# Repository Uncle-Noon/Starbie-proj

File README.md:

<h1>STARBOY</h1>  <br>
 
// my pcb <br> 

<br>
// original starbie image 

Starbie is a tiny motion-controlled digital pet: basically a desktop Tamagotchi with minimal gameplay buttons. Instead of pressing controls, you interact with it by physically moving the board. <br>

<h1><u>WHAT IT IS </u> <br></h1>

Starbie is designed to sit on your desk, show its personality on a small display, and react to how you handle it. Tilting, moving, and otherwise checking in on your pet are meant to be part of the experience.

The board includes a microcontroller, display, motion sensor, and environmental sensor in a compact PCB design. It is USB powered and built around beginner-friendly through-hole soldering for the add-on components. <br> 

<h3> Tutorial Link -> </h3>  https://github.com/SharKingStudios/Starbie/blob/main/README.md <br> <br> 
This is my github repo for HalfLife-HackClub program. Look into the tutorial link for more information. <br >
This repo contains my devlogs, required files, and the BOM with the Starbie.ino. <br>

{P.S. I named my project Starboy instead of Starbiee}

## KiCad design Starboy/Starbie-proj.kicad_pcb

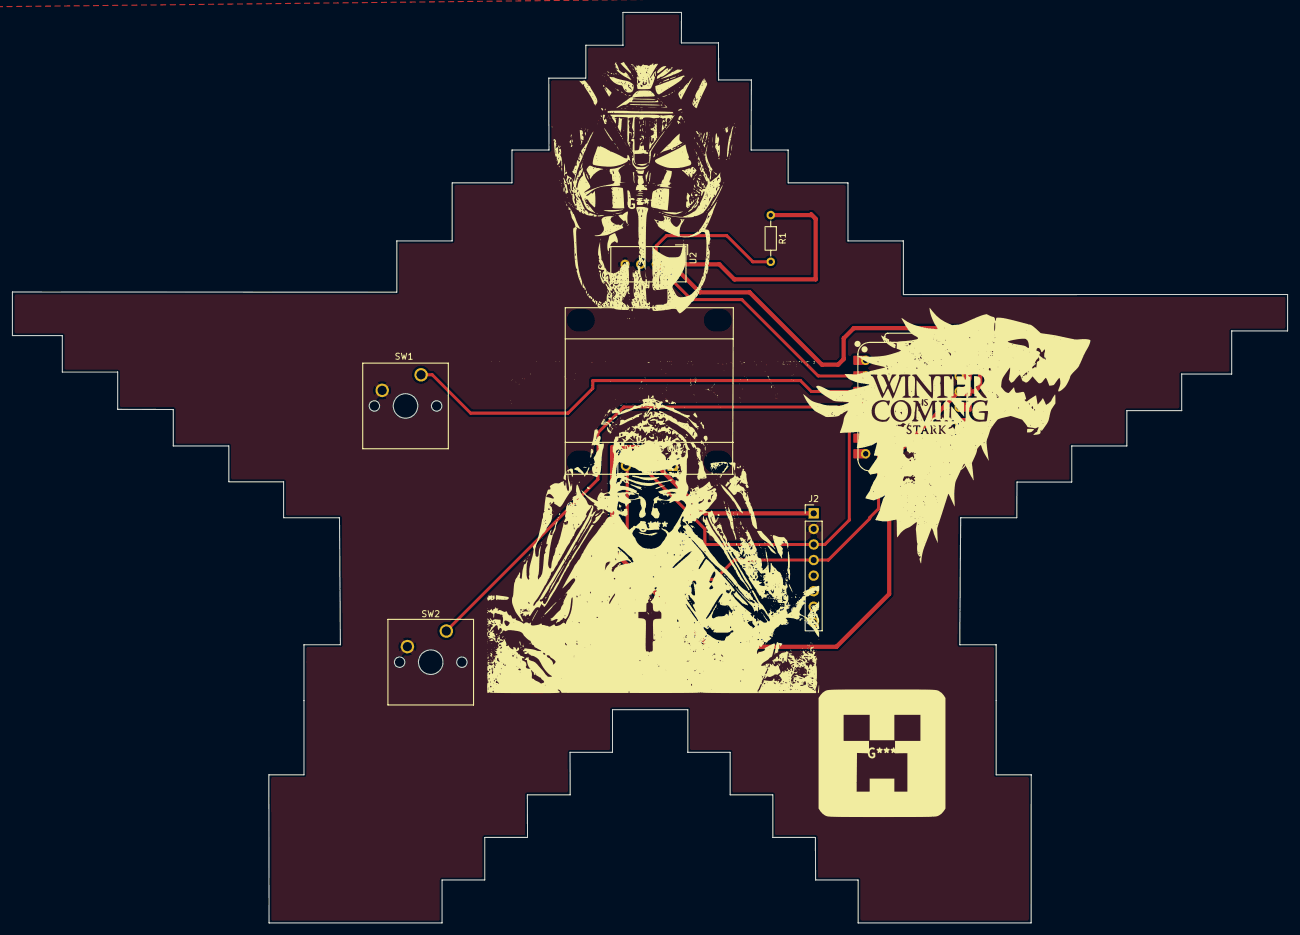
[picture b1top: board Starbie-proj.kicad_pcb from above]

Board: 2 copper layers, 208.1 x 148.6 mm, 7 parts (0 on the bottom side), 3 nets.

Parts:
J1: Conn_01x04_Pin; Display_128x64_096_I2C
J2: Conn_01x08_Pin; PinHeader_1x08_P2.54mm_Vertical
R1: 10k; R_Axial_DIN0204_L3.6mm_D1.6mm_P7.62mm_Horizontal
SW1, SW2: SW_Push; SW_Cherry_MX_1.00u_PCB
U1: XIAO-ESP32-C3-SMD; XIAO-ESP32-C6-DIP
U2: DHT11; Aosong_DHT11_5.5x12.0_P2.54mm

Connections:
+3.3V: J1.2, J2.1, R1.1, U1.12 (3V3_OUT), U2.1 (VDD)
/<NO NET>: J1.3, J1.4, J2.3, J2.4, R1.2, SW1.1, SW2.1, U1.2 (D1), U1.3 (D2), U1.4 (D3), U1.5 (D4), U1.6 (D5), U2.2 (DATA)
GND: J1.1, J2.2, SW1.2, SW2.2, U1.13 (GND), U2.4 (GND)
